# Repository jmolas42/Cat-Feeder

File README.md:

# Cat-Feeder

## Distributeur automatique de nourriture pour chat

Préparez-vous à une innovation majeure dans la gestion alimentaire de vos compagnons félins ! Le distributeur automatique pour chats est une solution ingénieuse qui prend en charge la nourriture de votre animal de compagnie de manière autonome et efficace. Plus besoin de vous soucier des repas de votre chat, laissez cet appareil révolutionnaire s'occuper de tout, vous offrant ainsi une tranquillité d'esprit totale. Avec cette technologie de pointe, simplifiez votre quotidien et offrez à votre félin une expérience alimentaire optimale, tout en vous concentrant sur les moments importants de la vie.

## Gestion automatique et sécurisée pour les repas de votre chat

### Fonctionnalités :
- **Entièrement configurable** : Ajustez les paramètres selon les besoins spécifiques de votre chat.
- **Distribution automatique des croquettes à certaines heures** : Assure une alimentation régulière et équilibrée.
- **Porte qui s’ouvre seulement pour le chat autorisé** : Grâce à une balise dans le cou du chat, garantissant un accès sécurisé à la nourriture.
- **Connecté au WiFi** : Permet une gestion à distance et synchronisation des horaires.
- **Balance intégrée** : Surveille le poids du bol et enregistre l’appétit du chat via un site web dédié.
- **Système de secours pour l’alimentation** : Fonctionne avec des piles en cas de coupure de courant, assurant une continuité de service.

## Installation et Configuration :
1. **Insérez les piles** dans le distributeur et la balise pour assurer leur bon fonctionnement.
2. **Configurez l'appareil** une fois pour définir les heures de distribution des repas et les paramètres personnalisés.
3. **Profitez** de la gestion automatisée des repas de votre chat, offrant une alimentation régulière et surveillée.

Avec le Cat-Feeder, offrez à votre félin une alimentation optimisée et simplifiez-vous la vie !

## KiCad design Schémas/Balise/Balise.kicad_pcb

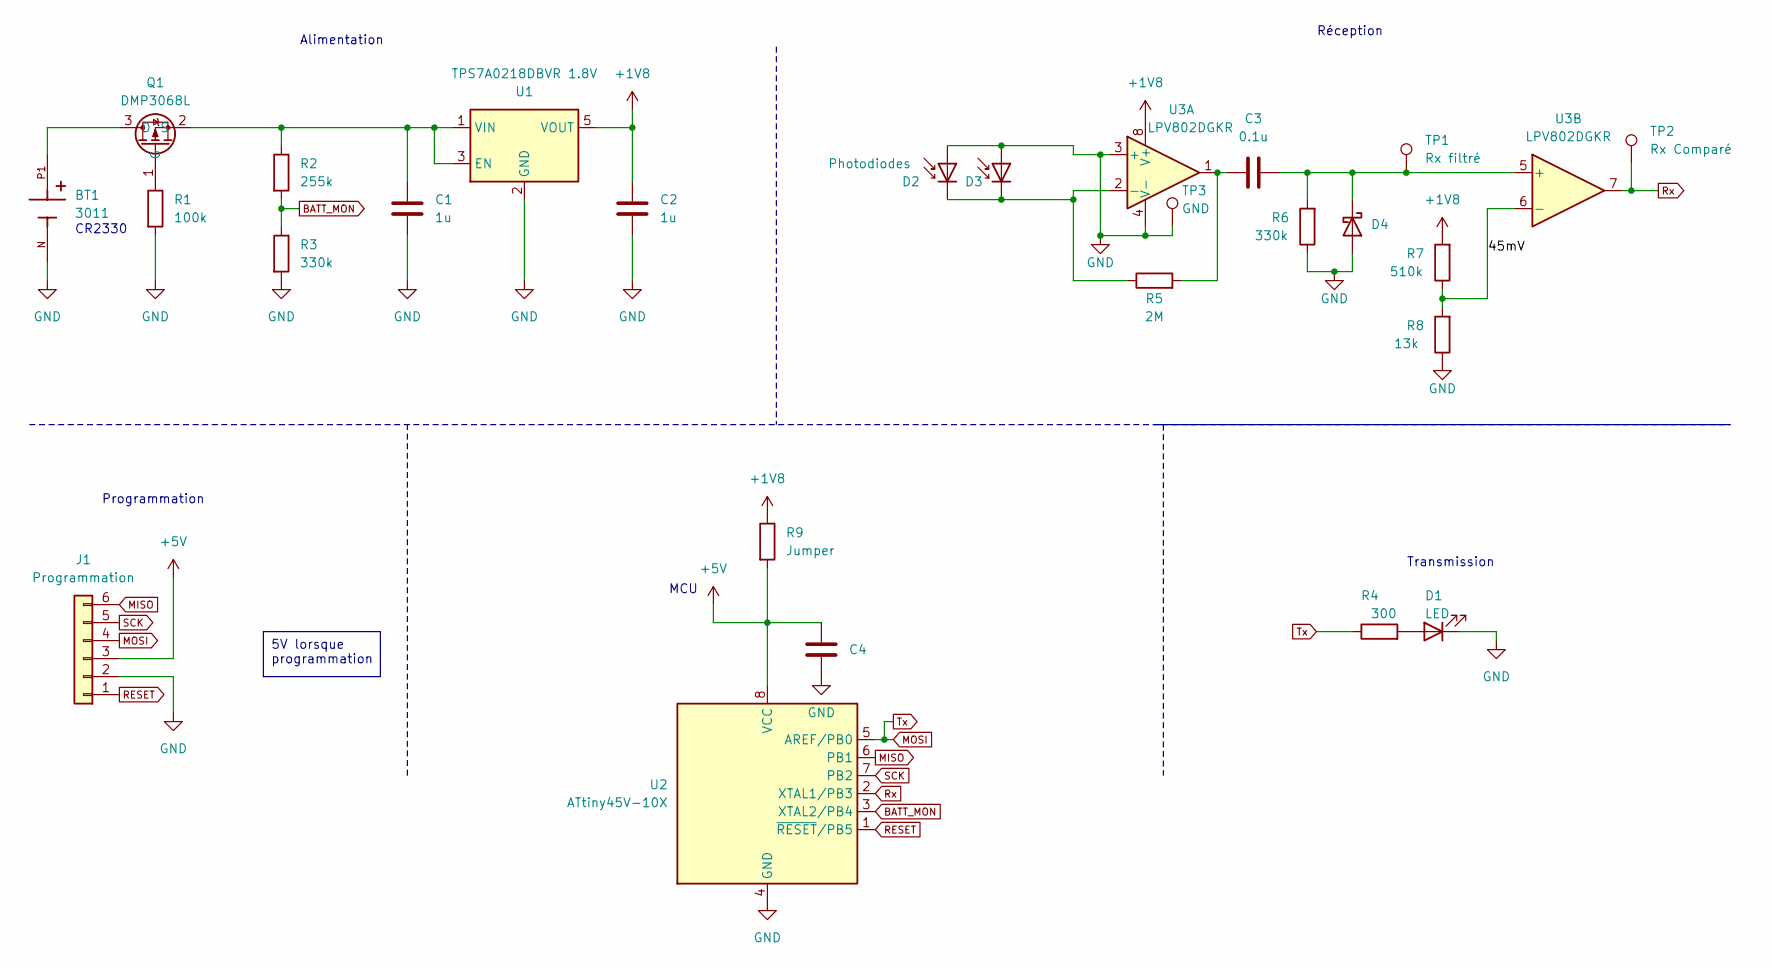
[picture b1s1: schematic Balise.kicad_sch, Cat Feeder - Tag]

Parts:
BT1: 3011; BAT_3011; PARTREV B
C1, C2: 1u; C_0603_1608Metric_Pad1.08x0.95mm_HandSolder
C3: 0.1u; C_0603_1608Metric_Pad1.08x0.95mm_HandSolder
C4: C_0603_1608Metric_Pad1.08x0.95mm_HandSolder
D1: LED; LED_0603_1608Metric_Pad1.05x0.95mm_HandSolder
D2: Photodiodes; LED_0805_2012Metric_Pad1.15x1.40mm_HandSolder
D3: D_Photo; LED_0805_2012Metric_Pad1.15x1.40mm_HandSolder
D4: D_Schottky; D_0603_1608Metric_Pad1.05x0.95mm_HandSolder
J1: Programmation; Tag-Connect_TC2030-IDC-NL_2x03_P1.27mm_Vertical
Q1: DMP3068L; SOT-23
R1: 100k; R_0603_1608Metric_Pad0.98x0.95mm_HandSolder
R2: 255k; R_0603_1608Metric_Pad0.98x0.95mm_HandSolder
R3, R6: 330k; R_0603_1608Metric_Pad0.98x0.95mm_HandSolder
R4: 300; R_0603_1608Metric_Pad0.98x0.95mm_HandSolder
R5: 2M; R_0603_1608Metric_Pad0.98x0.95mm_HandSolder
R7: 510k; R_0603_1608Metric_Pad0.98x0.95mm_HandSolder
R8: 13k; R_0603_1608Metric_Pad0.98x0.95mm_HandSolder
R9: Jumper; R_0603_1608Metric_Pad0.98x0.95mm_HandSolder
TP1: Rx filtré; HARWIN_S2751-46R
TP2: Rx Comparé; HARWIN_S2751-46R
TP3: GND; HARWIN_S2751-46R
U1: TPS7A0218DBVR 1.8V; TSOT-23-5
U2: ATtiny45V-10X; TSSOP-8_4.4x3mm_P0.65mm
U3: LPV802DGKR; VSSOP-8_3.0x3.0mm_P0.65mm

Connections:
+1V8: C2.1, R7.2, R9.1, U1.5 (VOUT), U3.8 (V+)
+5V: C4.1, J1.3, R9.2, U2.8 (VCC)
/45mV: R7.1, R8.2, U3.6 (-)
BATT_MON: R2.2, R3.1, U2.3 (XTAL2/PB4)
GND: BT1.N, C1.2, C2.2, C4.2, D1.1 (K), D2.2 (A), D3.2 (A), D4.2 (A), J1.2, R1.2, R3.2, R6.1, R8.1, TP3.1, U1.2 (GND), U2.4 (GND), U3.3 (+), U3.4 (V-)
MISO: J1.6, U2.6 (PB1)
MOSI: J1.4, R4.1, U2.5 (AREF/PB0)
unnamed: C3.1, R5.2, U3.1
unnamed: D1.2 (A), R4.2
unnamed: D2.1 (K), D3.1 (K), R5.1, U3.2 (-)
unnamed: C3.2, D4.1 (K), R6.2, TP1.1, U3.5 (+)
unnamed: BT1.P1, Q1.3 (D)
unnamed: Q1.1 (G), R1.1
unnamed: C1.1, Q1.2 (S), R2.1, U1.1 (VIN), U1.3 (EN)
RESET: J1.1, U2.1 (~RESET/PB5)
Rx: TP2.1, U2.2 (XTAL1/PB3), U3.7
SCK: J1.5, U2.7 (PB2)

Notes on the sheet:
5V lorsque programmation
CR2330
MCU
Alimentation
Programmation
Transmission
Réception

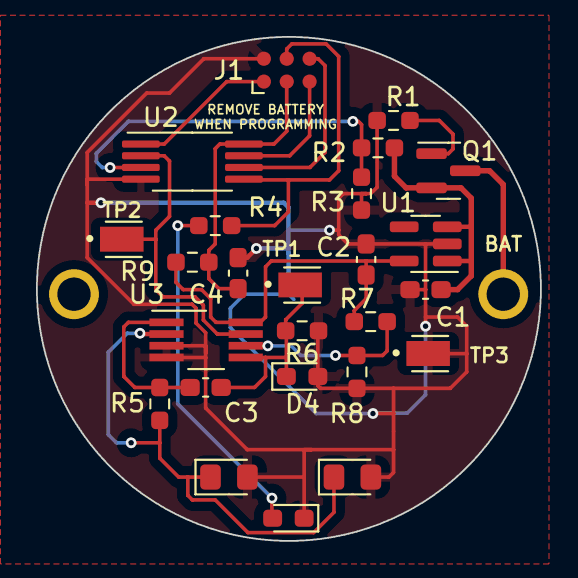
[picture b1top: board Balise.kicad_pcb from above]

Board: 2 copper layers, 28.0 x 28.0 mm, 26 parts (1 on the bottom side), 17 nets.

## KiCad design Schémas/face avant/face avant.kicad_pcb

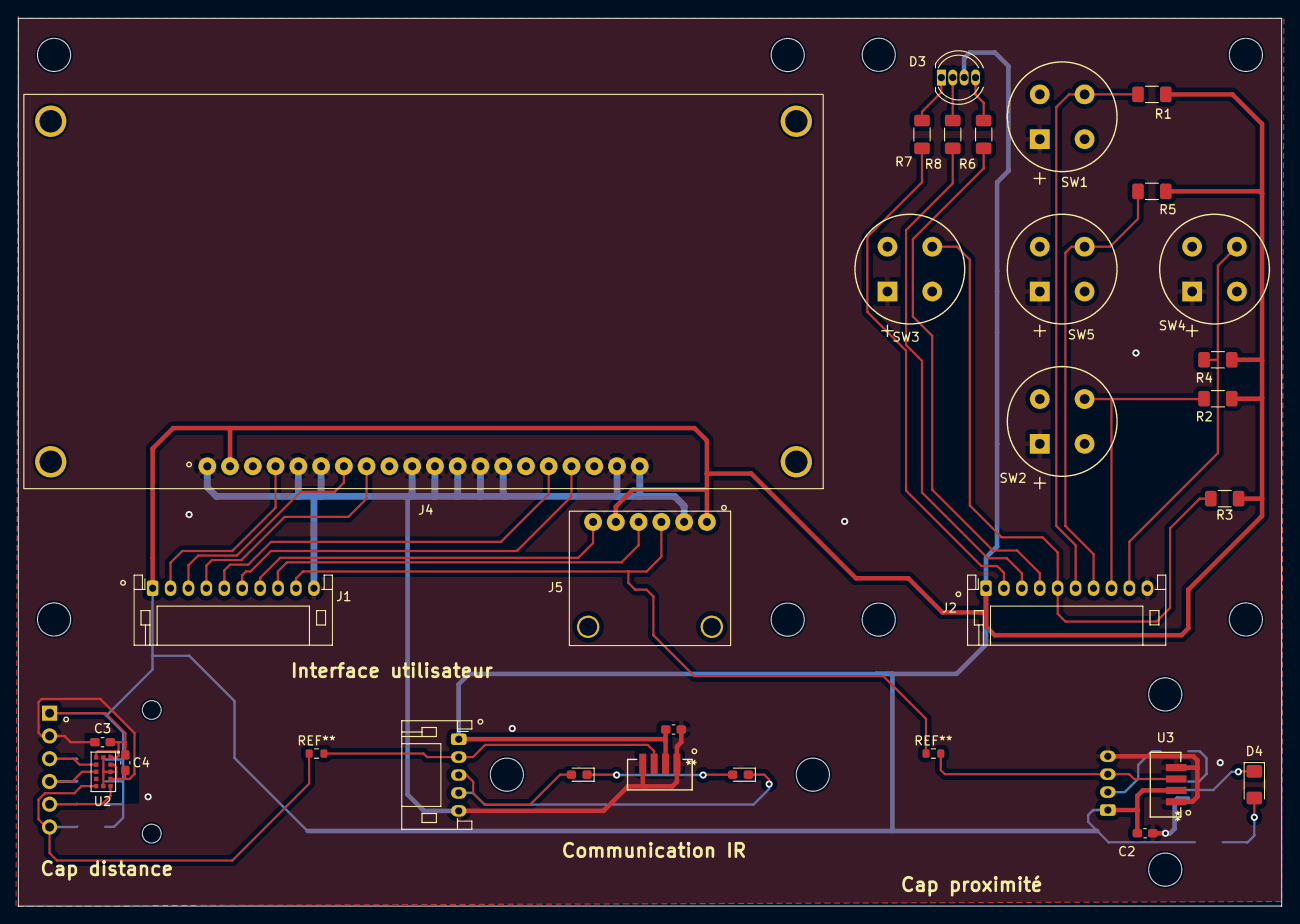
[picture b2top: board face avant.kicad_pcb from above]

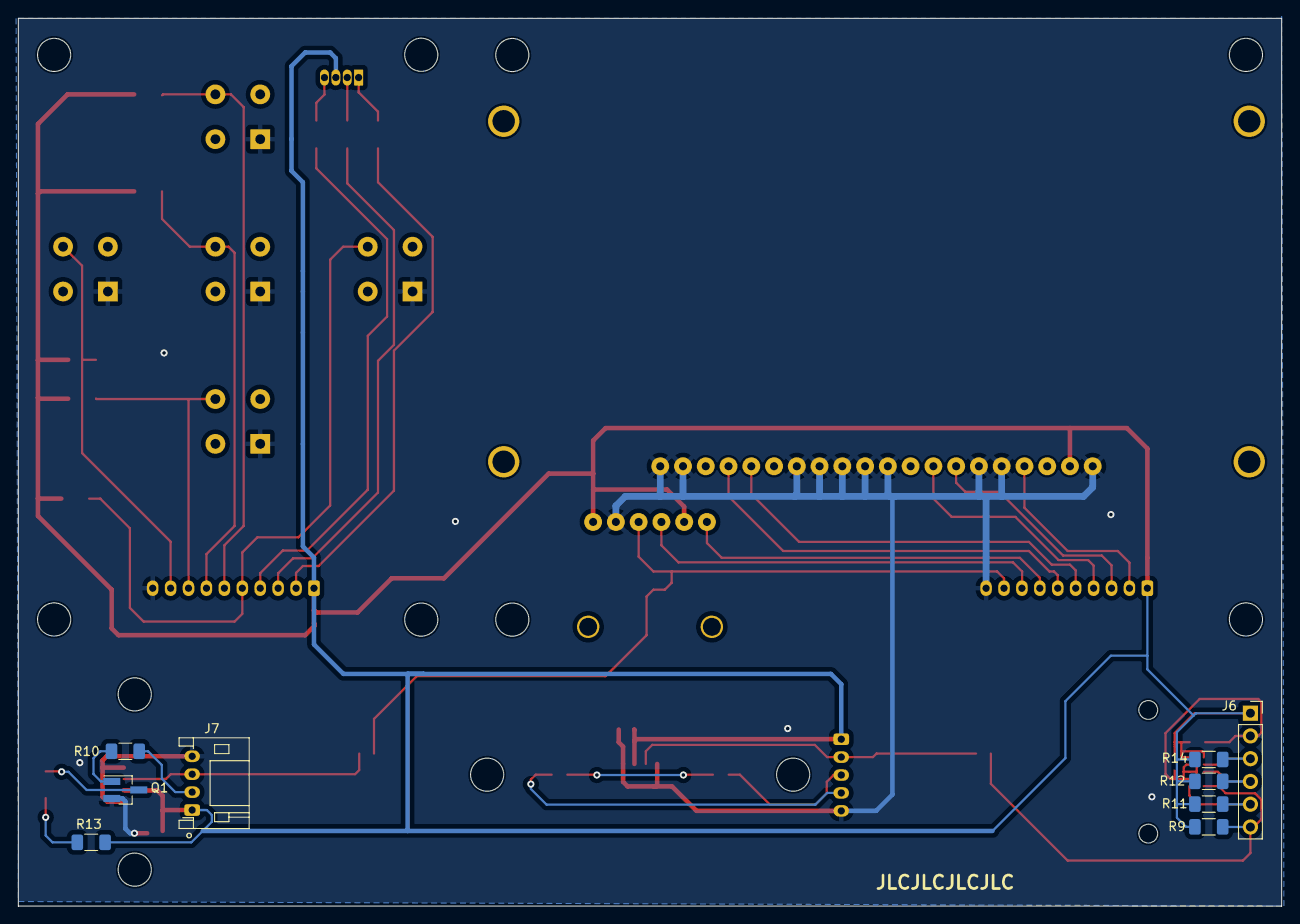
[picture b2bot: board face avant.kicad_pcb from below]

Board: 2 copper layers, 141.0 x 99.1 mm, 38 parts (9 on the bottom side), 34 nets.

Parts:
C1, C2: C_0603_1608Metric_Pad1.08x0.95mm_HandSolder
C3: 100n; C_0603_1608Metric_Pad1.08x0.95mm_HandSolder
C4: 4.7u; C_0603_1608Metric_Pad1.08x0.95mm_HandSolder
D1, D2: LED; LED_0603_1608Metric_Pad1.05x0.95mm_HandSolder
D3: QBL8RGB25C0; LED_D5.0mm-4_RGB
D4: LED; LED_1206_3216Metric_Pad1.42x1.75mm_HandSolder
J1, J2: Conn_01x10; JST_PH_S10B-PH-K_1x10_P2.00mm_Horizontal
J3: Conn_01x05; JST_PH_S5B-PH-K_1x05_P2.00mm_Horizontal
J4: NHD-3.12-25664UCW2; Screen
J5: vers VL53L4CDV0DH; Cap dist
J6: PinHeader_1x06_P2.54mm_Vertical
J7: Conn_01x04; JST_PH_S4B-PH-K_1x04_P2.00mm_Horizontal
Q1: PJA3432-AU_R1; SOT-23_Handsoldering
R1, R2, R3, R4, R5, R9, R11, R12, R14: 10k; R_1206_3216Metric_Pad1.30x1.75mm_HandSolder
R6, R7, R8: 220; R_1206_3216Metric_Pad1.30x1.75mm_HandSolder
R10: 100; R_1206_3216Metric_Pad1.30x1.75mm_HandSolder
R13: 40; R_1206_3216Metric_Pad1.30x1.75mm_HandSolder
SW1: Bouton haut; D6R_CNK
SW2: Bouton bas; D6R_CNK
SW3: Bouton gauche; D6R_CNK
SW4: Bouton droit; D6R_CNK
SW5: Bouton sélection; D6R_CNK
U1: TSOP75338TT; TSOP75338WTT_VIS-M
U2: VL53L4CDV0DH; XDCR_VL53L3CXV0DH_1
U3: TSOP75438WTR; TSOP75338WTT_VIS-M

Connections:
+3V3: C1.1, C2.1, C3.1, C4.1, D3.3 (A), J1.1, J2.1, J3.1, J4.2, J5.1, J5.5, J6.1, J7.1, R1.1, R2.1, R3.1, R4.1, R5.1, R9.2, R11.2, R12.2, R13.2, R14.2, U1.2 (VS), U2.1 (AVDDVCSEL), U2.11 (AVDD), U3.2 (VS)
BOUT_BAS: J2.8, R2.2, SW2.3
BOUT_DROIT: J2.9, R4.2, SW4.3
BOUT_GAUCHE: J2.5, R3.2, SW3.3
BOUT_HAUT: J2.6, R1.2, SW1.3
BOUT_SELECT: J2.7, R5.2, SW5.3
D/C_ecran: J1.2, J4.4
GND: C1.2, C2.2, C3.2, C4.2, J1.10, J2.10, J3.5, J4.1, J4.5, J4.6, J4.10, J4.11, J4.12, J4.13, J4.14, J4.19, J4.20, J5.2, J6.2, J7.4, Q1.2 (S), SW1.1, SW2.1, SW3.1, SW4.1, SW5.1, U1.1 (GND), U1.4 (GND), U2.2 (AVSSVCSEL), U2.3 (GND), U2.4 (GND__1), U2.6 (GND__2), U2.12 (GND__3), U3.1 (GND), U3.4 (GND)
INT_cap-dis: J1.7, J5.6
unnamed: D1.2 (A), J3.3
unnamed: D1.1 (K), D2.2 (A)
unnamed: D2.1 (K), J3.4
unnamed: D3.2 (BK), R8.2
unnamed: D3.1 (GK), R7.2
unnamed: D3.4 (RK), R6.2
unnamed: D4.2 (A), R13.1
unnamed: D4.1 (K), Q1.3 (D)
unnamed: J3.2, U1.3 (OUT)
unnamed: J6.3, R14.1, U2.10 (SCL)
unnamed: J6.4, R12.1, U2.9 (SDA)
unnamed: J6.5, R11.1, U2.5 (XSHUT)
unnamed: J6.6, R9.1, U2.7 (GPIO1)
unnamed: J7.2, R10.1
unnamed: J7.3, U3.3 (OUT)
unnamed: Q1.1 (G), R10.2
RGB_B: J2.3, R8.1
RGB_G: J2.2, R7.1
RGB_R: J2.4, R6.1
SCLK_ecran: J1.3, J4.7
SCL_cap-dis: J1.9, J5.3
SDA_cap-dis: J1.8, J5.4
SDIN_ecran: J1.4, J4.8
/CS_ecran: J1.6, J4.17
/RES_ecran: J1.5, J4.16

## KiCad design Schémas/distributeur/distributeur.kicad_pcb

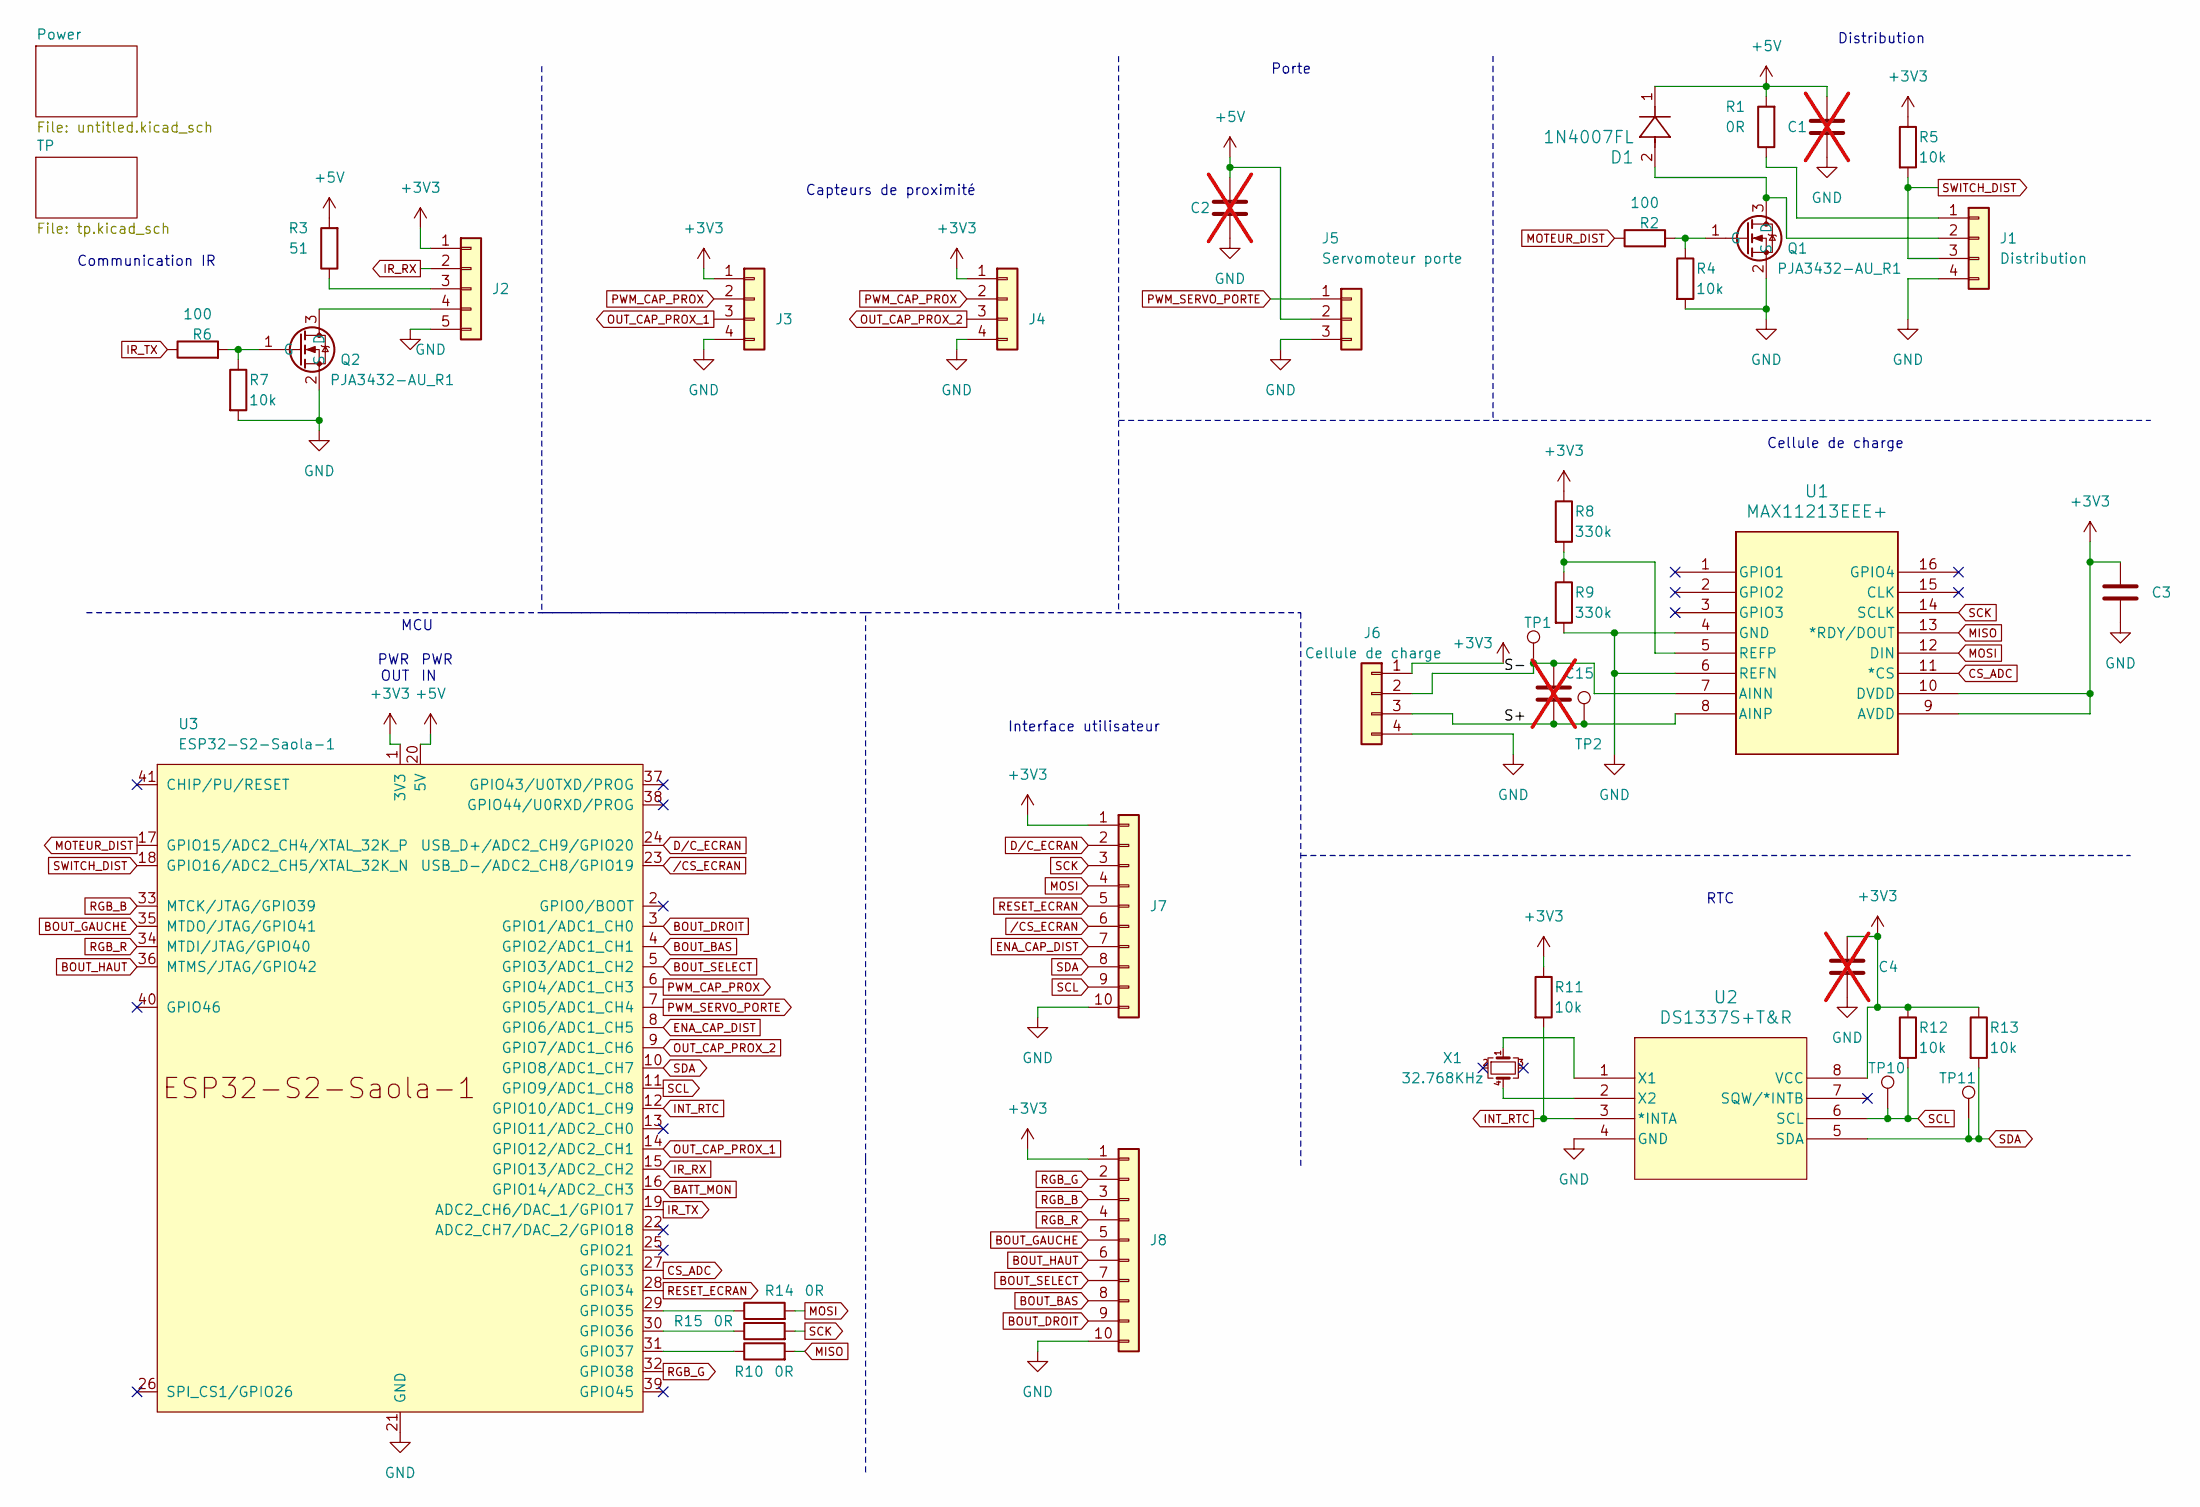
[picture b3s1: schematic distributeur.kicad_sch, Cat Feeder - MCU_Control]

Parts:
C1, C2, C4, C15: C_0603_1608Metric_Pad1.08x0.95mm_HandSolder; not fitted
C3: C_0603_1608Metric_Pad1.08x0.95mm_HandSolder
D1: 1N4007FL; CR_SOD-123FL_SME-M
J1: Distribution; PinHeader_1x04_P2.54mm_Vertical
J2: JST_PH_B5B-PH-K_1x05_P2.00mm_Vertical
J3, J4: JST_PH_B4B-PH-K_1x04_P2.00mm_Vertical
J5: Servomoteur porte; PinHeader_1x03_P2.54mm_Vertical
J6: Cellule de charge; PinHeader_1x04_P2.54mm_Vertical
J7, J8: Conn_01x10; JST_PH_B10B-PH-K_1x10_P2.00mm_Vertical
Q1, Q2: PJA3432-AU_R1; SOT-23_Handsoldering
R1: 0R; R_1206_3216Metric_Pad1.30x1.75mm_HandSolder
R2, R6: 100; R_1206_3216Metric_Pad1.30x1.75mm_HandSolder
R3: 51; R_1206_3216Metric_Pad1.30x1.75mm_HandSolder
R4, R5, R7, R11, R12, R13: 10k; R_1206_3216Metric_Pad1.30x1.75mm_HandSolder
R8, R9: 330k; R_1206_3216Metric_Pad1.30x1.75mm_HandSolder
R10, R14, R15: 0R; R_0805_2012Metric_Pad1.20x1.40mm_HandSolder
TP1, TP2, TP10, TP11: TP420X150
U1: MAX11213EEE+; 21-0055H_16_MXM-M
U2: DS1337S+T&R; 21-0041B_8_MXM-M
U3: ESP32-S2-Saola-1
X1: 32.768KHz; XTAL_ABS25-32.768KHZ-6-1-T

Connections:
+3V3: C3.1, C4.1, J2.1, J3.1, J4.1, J6.1, J7.1, J8.1, R5.1, R8.1, R11.1, R12.1, R13.1, U1.9 (AVDD), U1.10 (DVDD), U2.8 (VCC), U3.1 (3V3)
+5V: C1.1, C2.1, D1.1, J5.2, R1.2, R3.2, U3.20 (5V); also elsewhere on the board
/S+: C15.2, J6.3, TP2.1, U1.8 (AINP)
/S-: C15.1, J6.2, TP1.1, U1.7 (AINN)
BATT_MON: U3.16 (GPIO14/ADC2_CH3); also elsewhere on the board
BOUT_BAS: J8.8, U3.4 (GPIO2/ADC1_CH1)
BOUT_DROIT: J8.9, U3.3 (GPIO1/ADC1_CH0)
BOUT_GAUCHE: J8.5, U3.35 (MTDO/JTAG/GPIO41)
BOUT_HAUT: J8.6, U3.36 (MTMS/JTAG/GPIO42)
BOUT_SELECT: J8.7, U3.5 (GPIO3/ADC1_CH2)
CS_ADC: U1.11 (*CS), U3.27 (GPIO33)
D/C_ECRAN: J7.2, U3.24 (USB_D+/ADC2_CH9/GPIO20)
GND: C1.2, C2.2, C3.2, C4.2, J1.4, J2.5, J3.4, J4.4, J5.3, J6.4, J7.10, J8.10, Q1.2 (S), Q2.2 (S), R4.2, R7.2, R9.2, U1.4 (GND), U1.6 (REFN), U2.4 (GND), U3.21 (GND), U3.42 (GND); also elsewhere on the board
INT_CAP_DIST: J7.7, U3.8 (GPIO6/ADC1_CH5)
INT_RTC: R11.2, U2.3 (*INTA), U3.12 (GPIO10/ADC1_CH9)
IR_RX: J2.2, U3.15 (GPIO13/ADC2_CH2)
IR_TX: R6.1, U3.19 (ADC2_CH6/DAC_1/GPIO17)
MISO: R10.2, U1.13 (*RDY/DOUT); also elsewhere on the board
MOSI: J7.4, R14.2, U1.12 (DIN); also elsewhere on the board
MOTEUR_DIST: R2.1, U3.17 (GPIO15/ADC2_CH4/XTAL_32K_P)
unnamed: J1.1, R1.1
unnamed: D1.2, J1.2, Q1.3 (D)
unnamed: J2.3, R3.1
unnamed: J2.4, Q2.3 (D)
unnamed: Q1.1 (G), R2.2, R4.1
unnamed: Q2.1 (G), R6.2, R7.1
unnamed: R8.2, R9.1, U1.5 (REFP)
unnamed: U2.1 (X1), X1.1
unnamed: U2.2 (X2), X1.4
unnamed: R14.1, U3.29 (GPIO35)
unnamed: R15.1, U3.30 (GPIO36)
unnamed: R10.1, U3.31 (GPIO37)
OUT_CAP_PROX_1: J3.3, U3.14 (GPIO12/ADC2_CH1)
OUT_CAP_PROX_2: J4.3, U3.9 (GPIO7/ADC1_CH6)
PWM_CAP_PROX: J3.2, J4.2, U3.6 (GPIO4/ADC1_CH3)
PWM_SERVO_PORTE: J5.1, U3.7 (GPIO5/ADC1_CH4)
RESET_ECRAN: J7.5, U3.28 (GPIO34)
RGB_B: J8.3, U3.33 (MTCK/JTAG/GPIO39)
RGB_G: J8.2, U3.32 (GPIO38)
RGB_R: J8.4, U3.34 (MTDI/JTAG/GPIO40)
SCK: J7.3, R15.2, U1.14 (SCLK); also elsewhere on the board
SCL: J7.9, R12.2, TP10.1, U2.6 (SCL), U3.11 (GPIO9/ADC1_CH8)
SDA: J7.8, R13.2, TP11.1, U2.5 (SDA), U3.10 (GPIO8/ADC1_CH7)
SWITCH_DIST: J1.3, R5.2, U3.18 (GPIO16/ADC2_CH5/XTAL_32K_N)
/CS_ECRAN: J7.6, U3.23 (USB_D-/ADC2_CH8/GPIO19)

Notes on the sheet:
RTC
Porte
PWR IN
Communication IR
Distribution
Interface utilisateur
MCU
PWR OUT
Capteurs de proximité
Cellule de charge

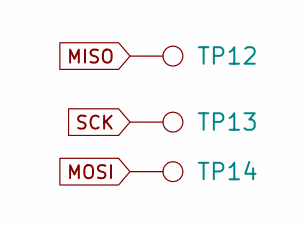
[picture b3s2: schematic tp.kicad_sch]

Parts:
TP12, TP13, TP14: TP420X150

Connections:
MISO: TP12.1; also elsewhere on the board
MOSI: TP14.1; also elsewhere on the board
SCK: TP13.1; also elsewhere on the board

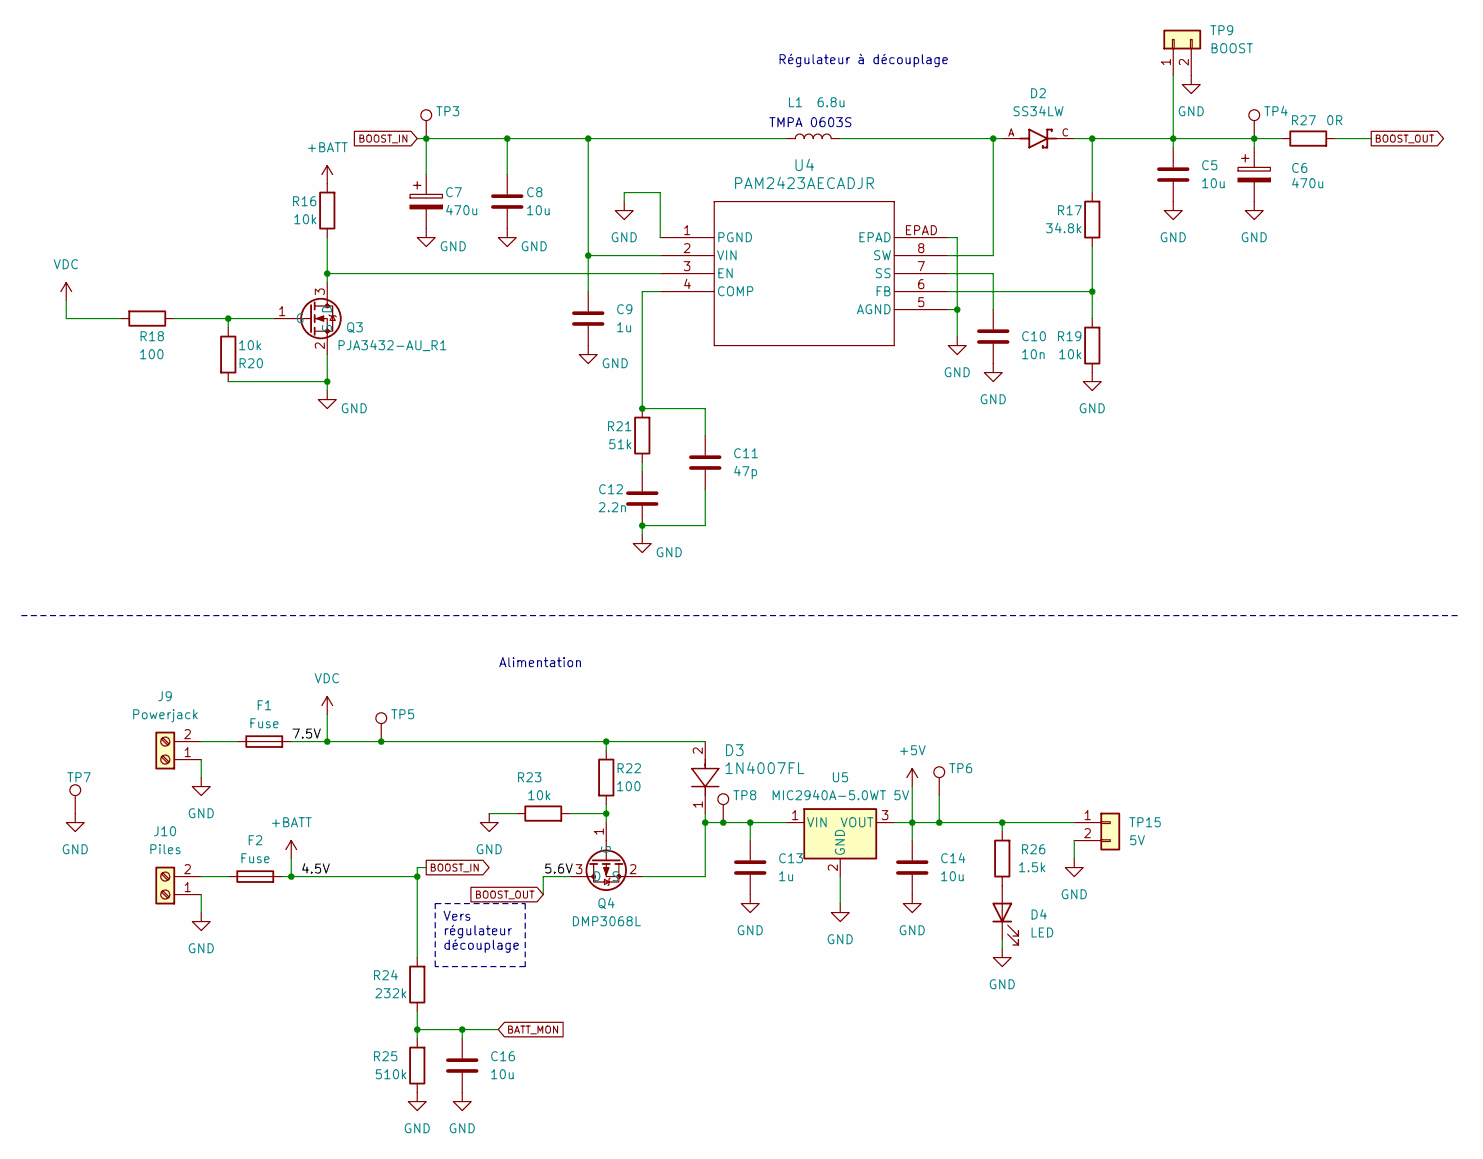
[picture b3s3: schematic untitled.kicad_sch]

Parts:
C5, C8: 10u; C_0805_2012Metric_Pad1.18x1.45mm_HandSolder
C6, C7: 470u; CAP_EEE_G_PAN-M
C9: 1u; C_0805_2012Metric_Pad1.18x1.45mm_HandSolder
C10: 10n; C_0805_2012Metric_Pad1.18x1.45mm_HandSolder
C11: 47p; C_0805_2012Metric_Pad1.18x1.45mm_HandSolder
C12: 2.2n; C_0805_2012Metric_Pad1.18x1.45mm_HandSolder
C13: 1u; C_1206_3216Metric_Pad1.33x1.80mm_HandSolder
C14, C16: 10u; C_1206_3216Metric_Pad1.33x1.80mm_HandSolder
D2: SS34LW; SODFL3718X102N; PARTREV S2311
D3: 1N4007FL; CR_SOD-123FL_SME-M
D4: LED; LED_0603_1608Metric_Pad1.05x0.95mm_HandSolder
F1, F2: Fuse; FUSE_SMDF050-2
J9: Powerjack; CONN_OSTVN02A150_OST
J10: Piles; CONN_OSTVN02A150_OST
L1: 6.8u; TMPA 0603S
Q3: PJA3432-AU_R1; SOT-23_Handsoldering
Q4: DMP3068L; SOT-23_Handsoldering
R16, R19, R20, R23: 10k; R_0805_2012Metric_Pad1.20x1.40mm_HandSolder
R17: 34.8k; R_0805_2012Metric_Pad1.20x1.40mm_HandSolder
R18, R22: 100; R_0805_2012Metric_Pad1.20x1.40mm_HandSolder
R21: 51k; R_0805_2012Metric_Pad1.20x1.40mm_HandSolder
R24: 232k; R_0805_2012Metric_Pad1.20x1.40mm_HandSolder
R25: 510k; R_0805_2012Metric_Pad1.20x1.40mm_HandSolder
R26: 1.5k; R_1206_3216Metric_Pad1.30x1.75mm_HandSolder
R27: 0R; R_0805_2012Metric_Pad1.20x1.40mm_HandSolder
TP3, TP4, TP5, TP6, TP7, TP8: TP420X150
TP9: BOOST; PinHeader_1x02_P2.54mm_Vertical
TP15: 5V; PinHeader_1x02_P2.54mm_Vertical
U4: PAM2423AECADJR; SOP-8_PAM2423AECADJR_DIO-M
U5: MIC2940A-5.0WT 5V; TO-220-3_Vertical

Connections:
+5V: C14.1, R26.2, TP6.1, TP15.1, U5.3 (VOUT); also elsewhere on the board
BATT_MON: C16.1, R24.1, R25.2; also elsewhere on the board
BOOST_IN: C7.1, C8.1, C9.1, F2.2, L1.1, R16.2, R24.2, TP3.1, U4.2 (VIN)
BOOST_OUT: Q4.3 (D), R27.2
GND: C5.2, C6.2, C7.2, C8.2, C9.2, C10.2, C11.2, C12.2, C13.2, C14.2, C16.2, D4.1 (K), J9.1, J10.1, Q3.2 (S), R19.1, R20.2, R23.1, R25.1, TP7.1, TP9.2, TP15.2, U4.1 (PGND), U4.5 (AGND), U4.EPAD, U5.2 (GND); also elsewhere on the board
unnamed: C12.1, R21.1
unnamed: D4.2 (A), R26.1
unnamed: F1.1, J9.2
unnamed: F2.1, J10.2
unnamed: Q3.3 (D), R16.1, U4.3 (EN)
unnamed: Q3.1 (G), R18.1, R20.1
unnamed: Q4.1 (G), R22.2, R23.2
unnamed: C13.1, D3.1, Q4.2 (S), TP8.1, U5.1 (VIN)
unnamed: C5.1, C6.1, D2.C, R17.2, R27.1, TP4.1, TP9.1
unnamed: C11.1, R21.2, U4.4 (COMP)
unnamed: R17.1, R19.2, U4.6 (FB)
unnamed: C10.1, U4.7 (SS)
unnamed: D2.A, L1.2, U4.8 (SW)
VDC: D3.2, F1.2, R18.2, R22.1, TP5.1

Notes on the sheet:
Vers régulateur découplage
Alimentation
Régulateur à découplage
TMPA 0603S

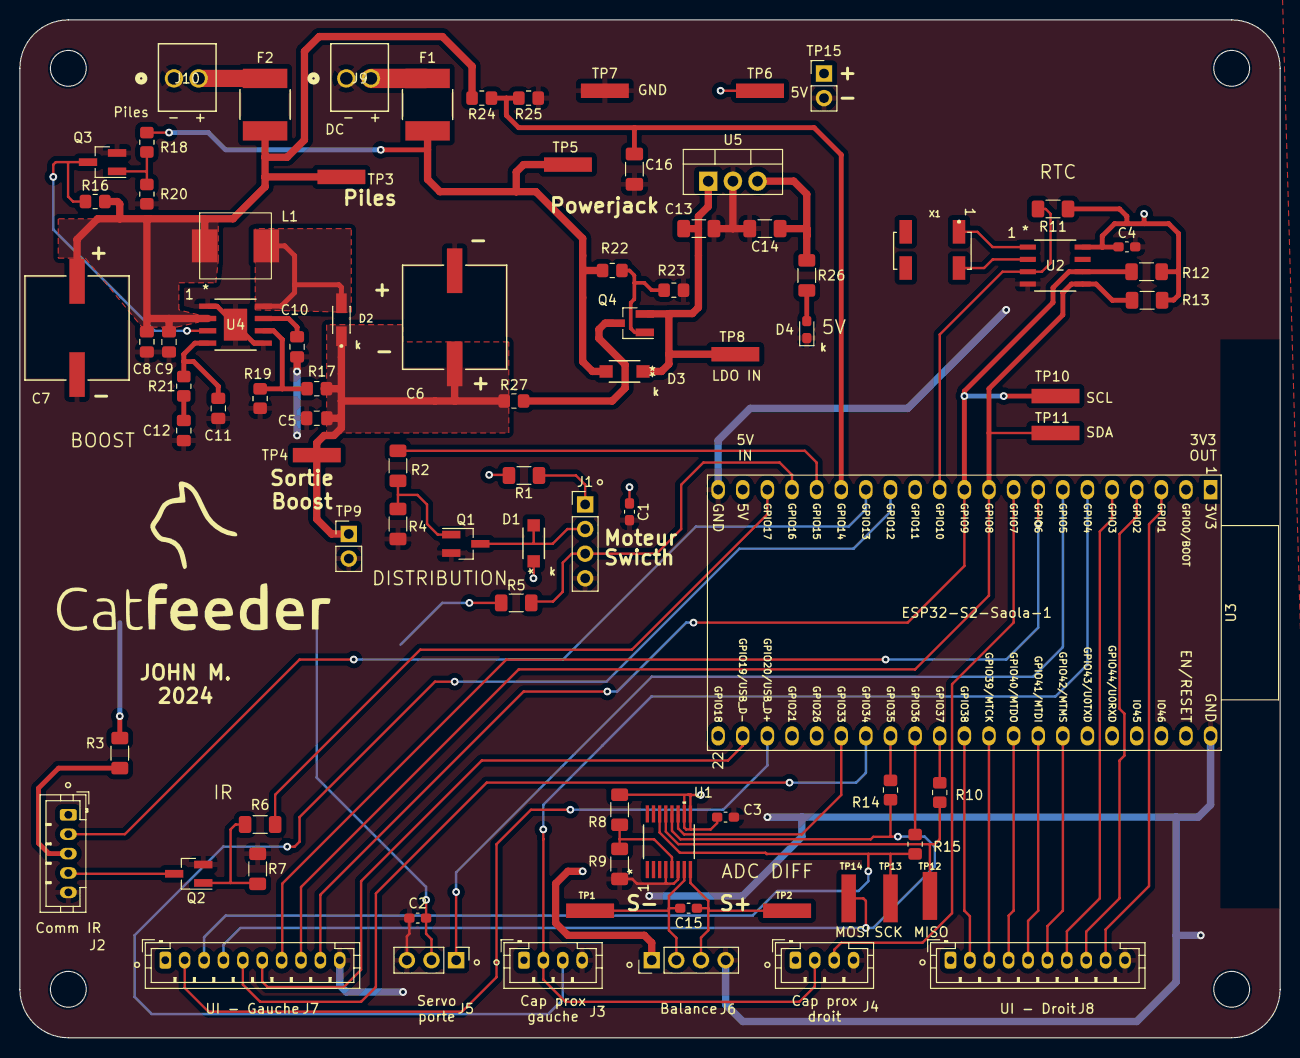
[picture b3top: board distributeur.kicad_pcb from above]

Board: 2 copper layers, 130.0 x 105.0 mm, 85 parts (0 on the bottom side), 61 nets.

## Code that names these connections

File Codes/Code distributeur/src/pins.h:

/*PINS*/

//Batterie
#define PIN_BATT_MON 14      //lecture voltage batterie

//Boutons
#define PIN_BUT_UP 42        //bouton haut
#define PIN_BUT_DOWN 2       //bouton bas
#define PIN_BUT_LEFT 41      //bouton gauche
#define PIN_BUT_RIGHT 1      //bouton droit
#define PIN_BUT_SELECT 3     //bouton sélection

//Écran
#define PIN_DC_SCREEN 20     //DC écran
#define PIN_CS_SCREEN 19     //chip select écran
#define PIN_RESET_SCREEN 34  //reset écran

//RGB
#define PIN_RGB_R 40         //RGB rouge
#define PIN_RGB_G 38         //RGB vert
#define PIN_RGB_B 39         //RGB bleu

//IR
#define PIN_IR_RX 13         //photorécepteur
#define PIN_IR_TX 17         //DEL IR

//Capteur de proximité
#define PIN_OUT_PROX_1 12    //photorécepteur capteur de proximité 1
#define PIN_OUT_PROX_2 7     //photorécepteur capteur de proximité 2
#define PIN_IN_PROX 4        //DEL capteurs de proximité (même signal pour les deux)

//Capteur de distance
#define PIN_XSHUT_DIST 6       //xshut capteur de distance

//Comm série
#define PIN_SDA 8            //SDA
#define PIN_SCL 9            //SCL
#define PIN_MOSI 35          //MOSI
#define PIN_MISO 37          //MISO
#define PIN_SCK 36           //SCK

//ADC balance
#define PIN_CS_ADC_SCALE 33  //chip select adc différentiel

//RTC
#define PIN_INT_RTC 10       //interrupt RTC

//Servo porte
#define PIN_SERVO 5          //servomoteur porte

//Distribution
#define PIN_MOTOR_DIST 15    //activation moteur distribution
#define PIN_SWITCH_DIST 16   //rétroaction moteur distribution

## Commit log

2024-03-25 change pins
2024-03-25 chg pins cap dist
2024-03-25 all pins in a file
2024-03-25 pins.h espace
2024-04-02 RTC base done
2024-04-02 print ip
2024-04-02 timeout wifi
2024-04-02 rtc optionnel wifi
2024-04-03 add balance
2024-04-03 test IR
2024-04-03 time main menu
2024-04-03 time refresh UI
2024-04-03 test comm IR
2024-04-03 ajout distribution
2024-04-03 fix distribution menu action
2024-04-03 servo porte
2024-04-05 IR fonctionnel
2024-04-10 comm IR fait
2024-04-10 comm IR ouvre porte
2024-04-10 comm IR machine etat, BUG chat mange
2024-04-10 comm IR marche 1st time only
2024-04-12 last session
2024-04-12 comm IR fonctionnel, mais compliqué
2024-04-14 comm IR fonctionnel
2024-04-15 comm IR fini!
2024-04-15 clear serial
2024-04-17 RTC fonctionnel
2024-04-17 rajout cap distance (buggy)
2024-04-17 fix temp cap dist
2024-04-17 menu portion done!
2024-04-17 base menu heure
2024-04-17 ajout fermeture écran
2024-04-17 door closes when open on reset
2024-04-17 UI presque fini
2024-04-18 distribution fini
2024-04-18 page de connection
2024-04-18 wifi AP logo et mode quitter
2024-04-19 balance fonctionnel
2024-04-19 fix sleep écran
2024-04-19 delai meilleur comm IR (millis)
2024-04-19 fix comm IR (close dist cap when ununsed)
2024-04-19 flash RGB rouge (à tester)
2024-04-19 RGB low battery fonctionnel
2024-04-22 influxDB_example
2024-04-22 inlfuxDB et poids
2024-04-24 poids sur influxdb
2024-04-24 Menu hour done
2024-04-24 fini menu action
2024-04-24 démarage de base
2024-04-24 fix wifi reconnect
2024-04-24 chg ordre loop
2024-04-25 fix lag cap distance
2024-04-25 bus spi plus vite
2024-04-25 bouton tare
2024-04-25 men acuueil batterie balise
2024-04-25 update poids 2 seconde plus tard
2024-04-25 adc faster
2024-04-25 fix distribution temporaire
2024-05-03 wifi reconnect
2024-05-08 last feeding updated
2024-05-08 update calibration load cell
2024-05-10 capt distance update range
2024-05-10 poids calib et délai
2024-05-10 fix main menu portions
2024-05-10 arrondi poids influxdb
2024-05-13 poids 50-50 a tester
2024-05-13 reset pour enlever
2024-05-13 verifynetwork au 20 sec pour demo
2024-05-13 reset => enlever
2024-05-13 detect network unconncted
2024-05-13 prefs ADC tare
2024-05-13 exclude neg weight real
2024-05-13 inlfuxdb float
2024-05-14 debug added
2024-05-20 chg calib
2024-05-20 chg timer screen off for demo
2024-05-22 structure github projet plus complet
2024-05-22 readme updated
2024-05-22 jpg to png
2024-05-22 path image
2024-05-22 ajout schema
2024-05-30 github repo final
2024-05-30 readme link photo
2024-05-30 link readme
